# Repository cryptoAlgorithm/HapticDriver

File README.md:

# HapticDriver

> Compact and over-engineered solenoid driver board for the purpose of generating localised haptic feedback.

## Features

* ESP32S3 module
* USB-C host port
* 12 MOSFET H-bridges with current regulation (up to 1A each)
* Powered by LiPo batteries (15V max)
* Extremely compact size - approx 6x3cm including antenna
* 4-layer PCB

---

## Description

This is a _work in progress_ driver board which has the capability to drive 12 solenoids bi-directionally
for the purpose of providing focused and precise haptic feedback. It's intended to be used in tendem with
a host application communicating over either WiFi or Bluetooth.

Due to the ESP module's limited number of GPIO, 3 8-bit shift registers over I2S were used to effectively
expand 3 I2S GPIO into 24 individually assignable outputs. This corresponds to the 24 H-bridge driver
inputs, which allow powering 12 electromagnets (forming solenoids) with regulated current of either
direction.

There is a 3V3 LDO regulator onboard for powering the logic bus - including the ESP32, shift registers
and motor driver logic power. It's powered through the battery power input, and provides up to 800mA and
has an absolute maximum voltage of 15V. Although the drivers tolerate a power input of up to 18V, the
LDO effectively limits the maximum battery input voltage to 15V. Care should be taken not to exceed this.

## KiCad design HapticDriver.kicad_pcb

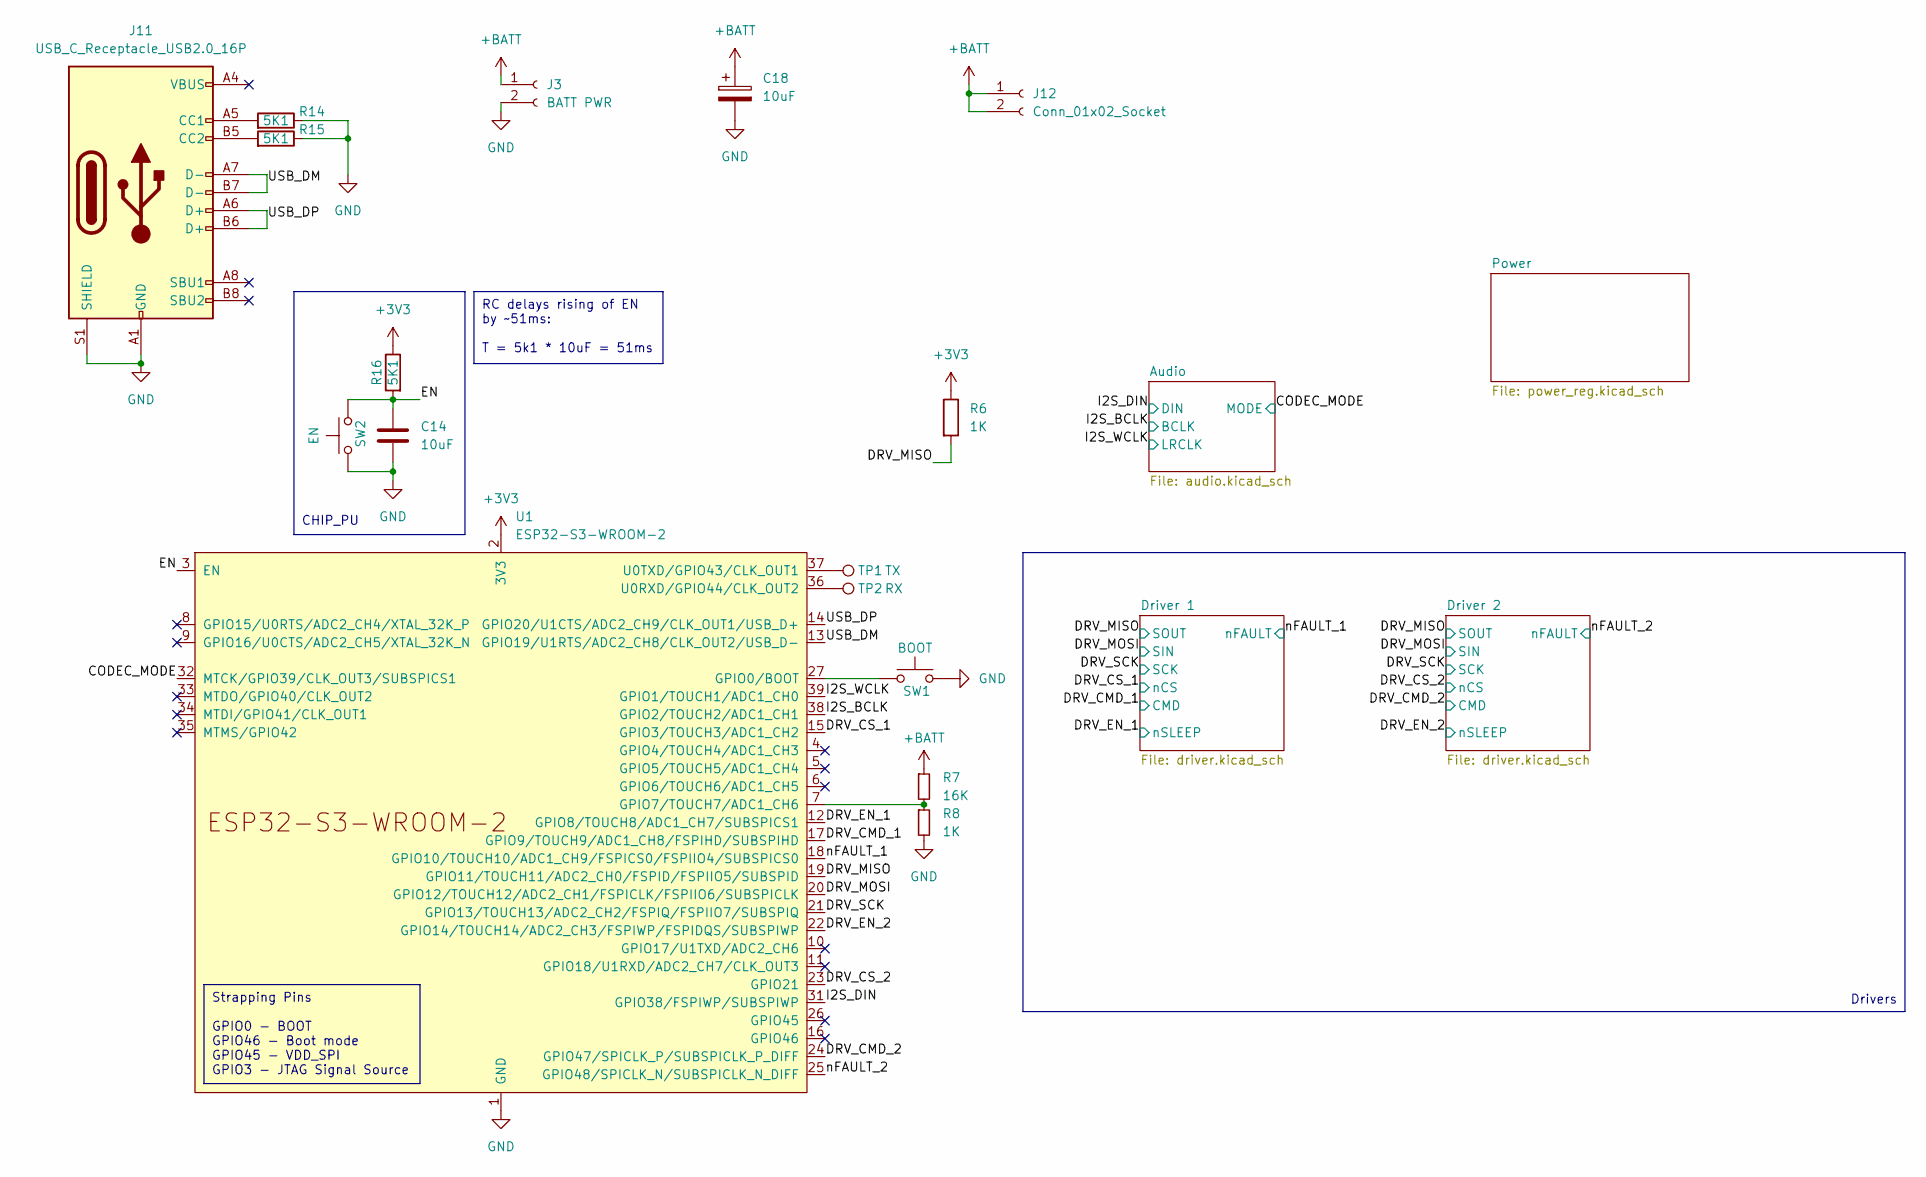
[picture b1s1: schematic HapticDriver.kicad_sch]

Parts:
C14: 10uF; C_0603_1608Metric; Part C96446
C18: 10uF; CP_Elec_4x5.4; Part C3001227
J3: BATT PWR; SolderWire-1sqmm_1x02_P5.4mm_D1.4mm_OD2.7mm
J11: USB_C_Receptacle_USB2.0_16P; USB_C_Receptacle_G-Switch_GT-USB-7010ASV; Part C2988369
J12: Conn_01x02_Socket; SolderWire_1x02
R6, R8: 1K; R_0402_1005Metric; Part C11702
R7: 16K; R_0402_1005Metric; Part C543609
R14, R15, R16: 5K1; R_0603_1608Metric; Part C2889415
SW1: BOOT; SW_Push_1P1T_XKB_TS-1187A; Part C318884
SW2: EN; SW_Push_1P1T_XKB_TS-1187A; Part C318884
TP1: TX; TestPoint_Pad_1.5x1.5mm
TP2: RX; TestPoint_Pad_1.5x1.5mm
U1: ESP32-S3-WROOM-2; ESP32-S3-WROOM-1; Part C2913202

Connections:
+3V3: R6.1, R16.1, U1.2 (3V3); also elsewhere on the board
+BATT: C18.1, J3.1, J12.1, J12.2, R7.1; also elsewhere on the board
/CODEC_MODE: U1.32 (MTCK/GPIO39/CLK_OUT3/SUBSPICS1); also elsewhere on the board
/DRV_CMD_1: U1.17 (GPIO9/TOUCH9/ADC1_CH8/FSPIHD/SUBSPIHD); also elsewhere on the board
/DRV_CMD_2: U1.24 (GPIO47/SPICLK_P/SUBSPICLK_P_DIFF); also elsewhere on the board
/DRV_CS_1: U1.15 (GPIO3/TOUCH3/ADC1_CH2); also elsewhere on the board
/DRV_CS_2: U1.23 (GPIO21); also elsewhere on the board
/DRV_EN_1: U1.12 (GPIO8/TOUCH8/ADC1_CH7/SUBSPICS1); also elsewhere on the board
/DRV_EN_2: U1.22 (GPIO14/TOUCH14/ADC2_CH3/FSPIWP/FSPIDQS/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); also elsewhere on the board
/DRV_MISO: R6.2, U1.19 (GPIO11/TOUCH11/ADC2_CH0/FSPID/FSPIIO5/S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); also elsewhere on the board
/DRV_MOSI: U1.20 (GPIO12/TOUCH12/ADC2_CH1/FSPICLK/FSPIIO6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); also elsewhere on the board
/DRV_SCK: U1.21 (GPIO13/TOUCH13/ADC2_CH2/FSPIQ/FSPIIO7/S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); also elsewhere on the board
/EN: C14.1, R16.2, SW2.2, U1.3 (EN)
/I2S_BCLK: U1.38 (GPIO2/TOUCH2/ADC1_CH1); also elsewhere on the board
/I2S_DIN: U1.31 (GPIO38/FSPIWP/SUBSPIWP); also elsewhere on the board
/I2S_WCLK: U1.39 (GPIO1/TOUCH1/ADC1_CH0); also elsewhere on the board
/USB_DM: J11.A7 (D-), J11.B7 (D-), U1.13 (GPIO19/U1RTS/ADC2_CH8/CLK_OUT2/USB_D-)
/USB_DP: J11.A6 (D+), J11.B6 (D+), U1.14 (GPIO20/U1CTS/ADC2_CH9/CLK_OUT1/USB_D+)
/nFAULT_1: U1.18 (GPIO10/TOUCH10/ADC1_CH9/FSPICS0/FSPIIO4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); also elsewhere on the board
/nFAULT_2: U1.25 (GPIO48/SPICLK_N/SUBSPICLK_N_DIFF); also elsewhere on the board
GND: C14.2, C18.2, J3.2, J11.A1 (GND), J11.A12 (GND), J11.B1 (GND), J11.B12 (GND), J11.S1 (SHIELD), R8.2, R14.1, R15.1, SW1.2, SW2.1, U1.1 (GND), U1.40 (GND), U1.41 (GND); also elsewhere on the board
unnamed: J11.A5 (CC1), R14.2
unnamed: J11.B5 (CC2), R15.2
unnamed: SW1.1, U1.27 (GPIO0/BOOT)
unnamed: R7.2, R8.1, U1.7 (GPIO7/TOUCH7/ADC1_CH6)
unnamed: TP2.1, U1.36 (U0RXD/GPIO44/CLK_OUT2)
unnamed: TP1.1, U1.37 (U0TXD/GPIO43/CLK_OUT1)

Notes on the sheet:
Strapping Pins GPIO0 - BOOT GPIO46 - Boot mode GPIO45 - VDD_SPI GPIO3 - JTAG Signal Source
RC delays rising of EN by ~51ms: T = 5k1 * 10uF = 51ms
Drivers
CHIP_PU

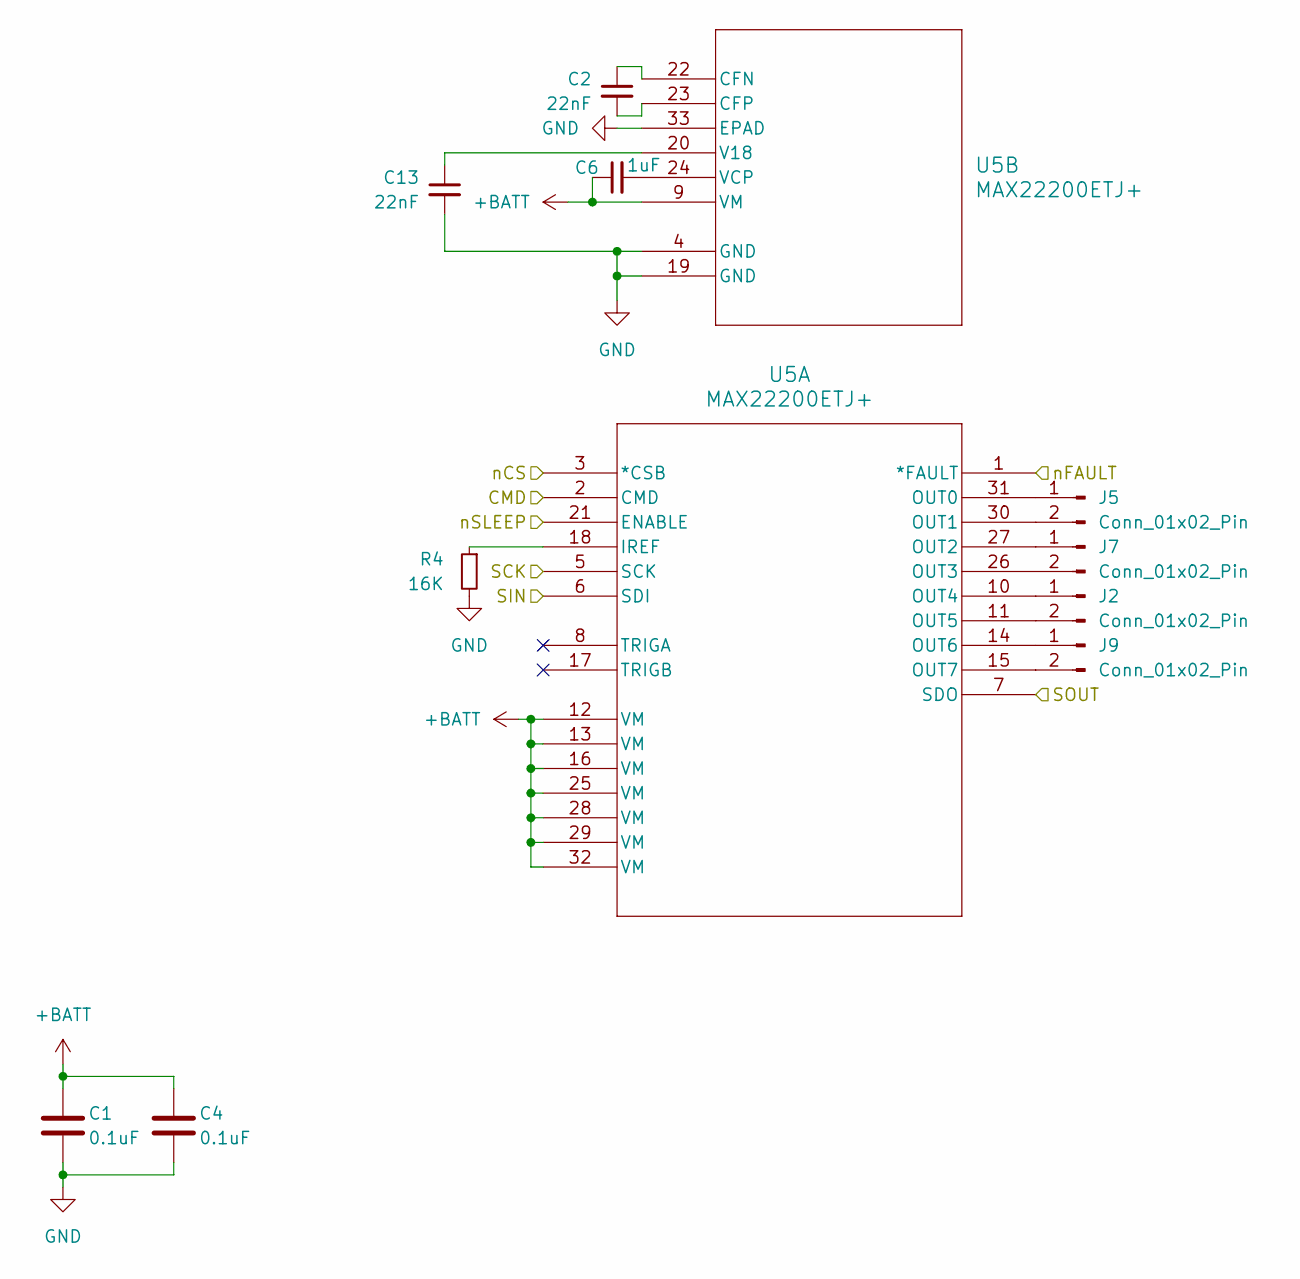
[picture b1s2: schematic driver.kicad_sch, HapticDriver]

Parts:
C1, C4: 0.1uF; C_0603_1608Metric; Part C14663
C2, C13: 22nF; C_0402_1005Metric; Part C1532
C6: 1uF; C_0402_1005Metric; Part C52923
J2, J5, J7, J9: Conn_01x02_Pin; SolderWire_1x02
R4: 16K; R_0402_1005Metric; Part C543609
U5: MAX22200ETJ+; 21-0140AK_T3255_8C_MXM; Part C2845158

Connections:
+BATT: C1.1, C4.1, C6.1, U5.9 (VM), U5.12 (VM), U5.13 (VM), U5.16 (VM), U5.25 (VM), U5.28 (VM), U5.29 (VM), U5.32 (VM); also elsewhere on the board
/DRV_CMD_1: U5.2 (CMD); also elsewhere on the board
/DRV_CS_1: U5.3 (*CSB); also elsewhere on the board
/DRV_EN_1: U5.21 (ENABLE); also elsewhere on the board
/DRV_MISO: U5.7 (SDO); also elsewhere on the board
/DRV_MOSI: U5.6 (SDI); also elsewhere on the board
/DRV_SCK: U5.5 (SCK); also elsewhere on the board
/nFAULT_1: U5.1 (*FAULT); also elsewhere on the board
GND: C1.2, C4.2, C13.2, R4.2, U5.4 (GND), U5.19 (GND), U5.33 (EPAD); also elsewhere on the board
unnamed: J2.1, U5.10 (OUT4)
unnamed: J2.2, U5.11 (OUT5)
unnamed: J5.1, U5.31 (OUT0)
unnamed: J5.2, U5.30 (OUT1)
unnamed: J7.1, U5.27 (OUT2)
unnamed: J7.2, U5.26 (OUT3)
unnamed: J9.1, U5.14 (OUT6)
unnamed: J9.2, U5.15 (OUT7)
unnamed: R4.1, U5.18 (IREF)
unnamed: C2.1, U5.22 (CFN)
unnamed: C2.2, U5.23 (CFP)
unnamed: C13.1, U5.20 (V18)
unnamed: C6.2, U5.24 (VCP)

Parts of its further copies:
C3, C12: 0.1uF; C_0603_1608Metric; Part C14663
C5, C15: 22nF; C_0402_1005Metric; Part C1532
C9: 1uF; C_0402_1005Metric; Part C52923
J4, J6, J8, J10: Conn_01x02_Pin; SolderWire_1x02
R5: 16K; R_0402_1005Metric; Part C543609
U6: MAX22200ETJ+; 21-0140AK_T3255_8C_MXM; Part C2845158

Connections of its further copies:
+BATT: C3.1, C9.1, C12.1, U6.9 (VM), U6.12 (VM), U6.13 (VM), U6.16 (VM), U6.25 (VM), U6.28 (VM), U6.29 (VM), U6.32 (VM); also elsewhere on the board
/DRV_CMD_2: U6.2 (CMD); also elsewhere on the board
/DRV_CS_2: U6.3 (*CSB); also elsewhere on the board
/DRV_EN_2: U6.21 (ENABLE); also elsewhere on the board
/DRV_MISO: U6.7 (SDO); also elsewhere on the board
/DRV_MOSI: U6.6 (SDI); also elsewhere on the board
/DRV_SCK: U6.5 (SCK); also elsewhere on the board
/nFAULT_2: U6.1 (*FAULT); also elsewhere on the board
GND: C3.2, C12.2, C15.2, R5.2, U6.4 (GND), U6.19 (GND), U6.33 (EPAD); also elsewhere on the board
unnamed: J4.1, U6.10 (OUT4)
unnamed: J4.2, U6.11 (OUT5)
unnamed: J6.1, U6.31 (OUT0)
unnamed: J6.2, U6.30 (OUT1)
unnamed: J8.1, U6.27 (OUT2)
unnamed: J8.2, U6.26 (OUT3)
unnamed: J10.1, U6.14 (OUT6)
unnamed: J10.2, U6.15 (OUT7)
unnamed: R5.1, U6.18 (IREF)
unnamed: C5.1, U6.22 (CFN)
unnamed: C5.2, U6.23 (CFP)
unnamed: C15.1, U6.20 (V18)
unnamed: C9.2, U6.24 (VCP)

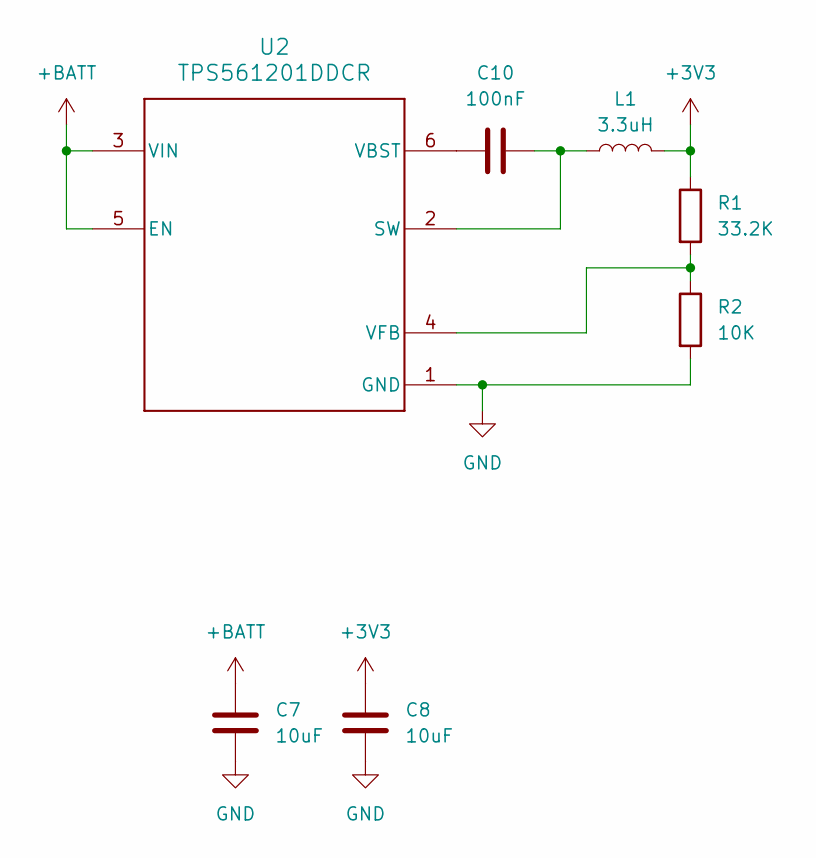
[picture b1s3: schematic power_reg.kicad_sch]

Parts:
C7, C8: 10uF; C_1206_3216Metric_Pad1.33x1.80mm_HandSolder; Part C13585
C10: 100nF; C_0603_1608Metric; Part C14663
L1: 3.3uH; L_Changjiang_FXL0530-3R3-M; Part C475518
R1: 33.2K; R_0603_1608Metric; Part C4216
R2: 10K; R_0603_1608Metric; Part C25804
U2: TPS561201DDCR; DDC0006A_N; Part C220433

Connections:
+3V3: C8.1, L1.2, R1.1; also elsewhere on the board
+BATT: C7.1, U2.3 (VIN), U2.5 (EN); also elsewhere on the board
GND: C7.2, C8.2, R2.2, U2.1 (GND); also elsewhere on the board
unnamed: C10.2, L1.1, U2.2 (SW)
unnamed: C10.1, U2.6 (VBST)
unnamed: R1.2, R2.1, U2.4 (VFB)

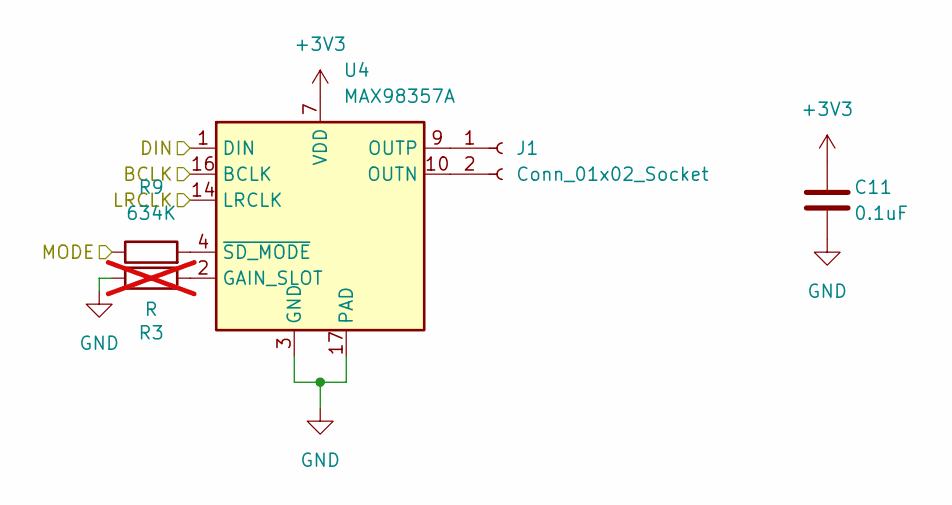
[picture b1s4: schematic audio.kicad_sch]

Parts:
C11: 0.1uF; C_0603_1608Metric; Part C14663
J1: Conn_01x02_Socket; SolderWire_1x02
R3: R; R_0402_1005Metric; not fitted
R9: 634K; R_0402_1005Metric; Part C227175
U4: MAX98357A; TQFN-16-1EP_3x3mm_P0.5mm_EP1.23x1.23mm; Part C910544

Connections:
+3V3: C11.1, U4.7 (VDD), U4.8 (VDD); also elsewhere on the board
/CODEC_MODE: R9.1; also elsewhere on the board
/I2S_BCLK: U4.16 (BCLK); also elsewhere on the board
/I2S_DIN: U4.1 (DIN); also elsewhere on the board
/I2S_WCLK: U4.14 (LRCLK); also elsewhere on the board
GND: C11.2, R3.1, U4.3 (GND), U4.11 (GND), U4.15 (GND), U4.17 (PAD); also elsewhere on the board
unnamed: J1.1, U4.9 (OUTP)
unnamed: J1.2, U4.10 (OUTN)
unnamed: R3.2, U4.2 (GAIN_SLOT)
unnamed: R9.2, U4.4 (~SD_MODE)

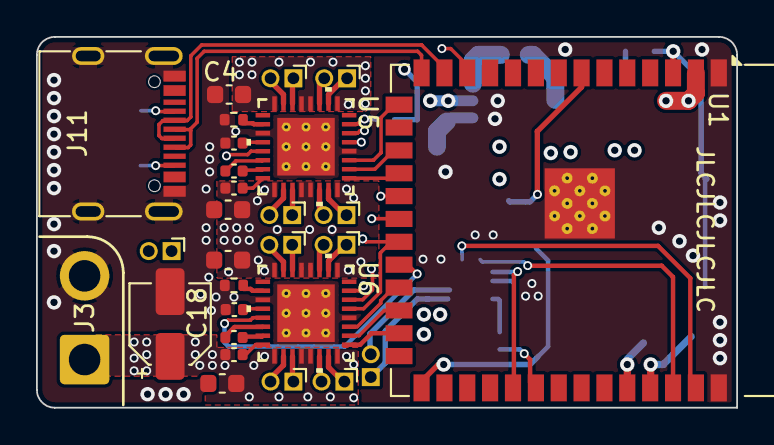
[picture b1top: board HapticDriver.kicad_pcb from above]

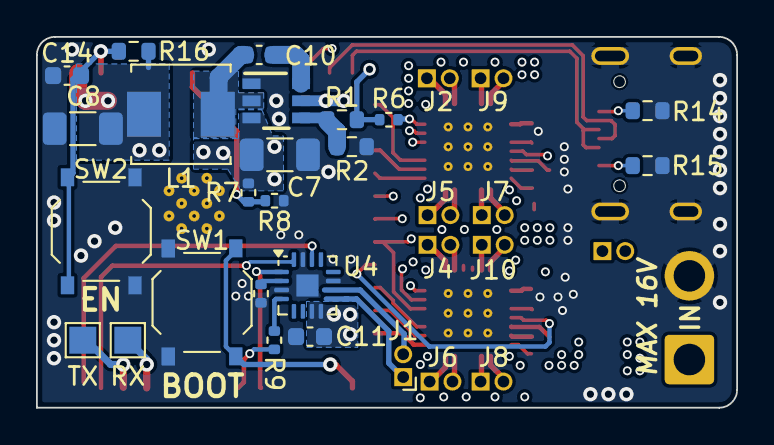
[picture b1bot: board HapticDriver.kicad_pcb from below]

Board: 4 copper layers, 38.9 x 20.6 mm, 50 parts (23 on the bottom side), 60 nets.

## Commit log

2023-12-21 feat: intial commit, mostly complete v0.1 design
2023-12-21 patch: ignore KiCad working files
2023-12-21 feat: add README
2023-12-21 patch: remove ignored files
2023-12-21 feat: pull OE and CLR shift reg pins to correct voltages
2023-12-21 patch: mark unused pins
2023-12-22 fix: avoid SDA on strapping pin GPIO45
2023-12-22 patch: specify value of sense resistor
2023-12-22 fix: delay rising of EN with cap, as per devkit design
2023-12-22 patch: improve silkscreen, add testpoints, optimise some traces
2023-12-23 patch: final touch-ups, v0.1 fabrication
2024-05-04 feat: major redesign with better driver and audio, partial routing
2024-05-28 feat: full reroute with max22200 driver
2024-05-29 feat: fully routed v2 design
2024-06-27 feat: battery level measurement resistors
2024-06-30 feat: populate all jlcpcb part#
